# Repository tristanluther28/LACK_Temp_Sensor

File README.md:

# LACK_Temp_Sensor
 Temperature sensor (LM335) with a 4 digit Seven Segment Display (LTC) output for the LACK 3D Printer Enclosure
 
 Read the full article and motivation here: https://tristanluther.com/projects/lack/

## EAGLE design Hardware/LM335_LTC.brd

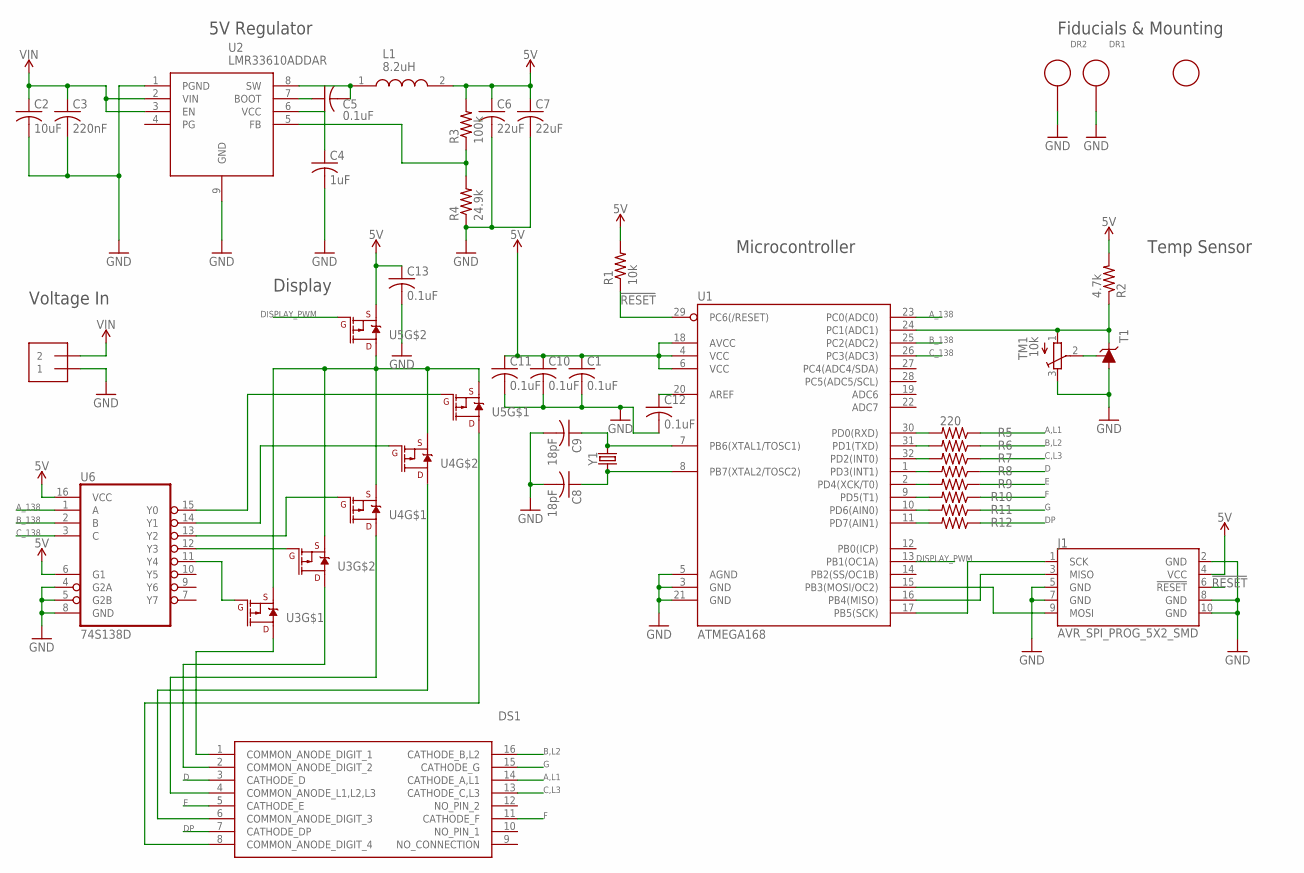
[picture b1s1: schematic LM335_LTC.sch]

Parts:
C1, C5, C10, C11, C12, C13: 0.1uF; C0805
C2: 10uF; C0805
C3: 220nF; C0805
C4: 1uF; C0805
C6, C7: 22uF; C0805
C8, C9: 18pF; C0805
DR1, DR2: 3MM_DRILL_GND
DS1: LTC-4627WC; DIPS1016W50P254L4018H725Q16N
J1: AVR_SPI_PROG_5X2_SMD; SAMTECH_FTSH-105-01
L1: 8.2uH; INDPM5752X150N
R1: 10k; R0805
R2: 4.7k; R0805
R3: 100k; R0805
R4: 24.9k; R0805
R5, R6, R7, R8, R9, R10, R11, R12: 220; R0805
T1: LM335; TO92
TM1: 10k; TC33X
U1: ATMEGA168; TQFP32-08
U2: LMR33610ADDAR; SOIC127P600X170-9N
U3, U4, U5: SI1967DH-T1-E3; SOT363_PHILIPS
U6: 74S138D; SO16
U$2: 25-B200-02; 25−B200-02
U$4: FIDUCIAL; FIDUCIAL_1MM
Y1: 16MHz; CRYSTAL-SMD-5X3.2-4PAD

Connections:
5V: C1.1, C6.1, C7.1, C10.1, C11.1, C13.1, J1.4 (VCC), L1.2, R1.2, R2.2, R3.2, U1.4 (VCC), U1.6 (VCC), U1.18 (AVCC), U5.4 (S), U6.6 (G1), U6.16 (VCC)
!RESET: J1.6 (!RESET), R1.1, U1.29 (PC6(/RESET))
A,L1: DS1.14 (CATHODE_A,L1), R5.1
A_138: U1.23 (PC0(ADC0)), U6.1 (A)
B,L2: DS1.16 (CATHODE_B,L2), R6.1
B_138: U1.25 (PC2(ADC2)), U6.2 (B)
C,L3: DS1.13 (CATHODE_C,L3), R7.1
C_138: U1.26 (PC3(ADC3)), U6.3 (C)
D: DS1.3 (CATHODE_D), R8.1
DISPLAY_PWM: U1.13 (PB1(OC1A)), U5.5 (G)
DP: DS1.7 (CATHODE_DP), R12.1
E: DS1.5 (CATHODE_E), R9.1
F: DS1.11 (CATHODE_F), R10.1
G: DS1.15 (CATHODE_G), R11.1
GND: C1.2, C2.2, C3.2, C4.2, C6.2, C7.2, C8.2, C9.2, C10.2, C11.2, C12.2, C13.2, DR1.DR, DR2.DR, J1.2 (GND), J1.5 (GND), J1.7 (GND), J1.8 (GND), J1.10 (GND), R4.1, T1.2 (A), TM1.3 (E), U1.3 (GND), U1.5 (AGND), U1.21 (GND), U2.1 (PGND), U2.9 (GND), U6.4 (G2A), U6.5 (G2B), U6.8 (GND), U$2.P1 (1)
unnamed: C4.1, U2.6 (VCC)
unnamed: R3.1, R4.2, U2.5 (FB)
unnamed: U3.2 (G), U6.11 (Y4)
unnamed: R2.1, T1.1 (C), TM1.1 (A), U1.24 (PC1(ADC1))
unnamed: C5.2, L1.1, U2.8 (SW)
unnamed: C5.1, U2.7 (BOOT)
unnamed: T1.3 (ADJ), TM1.2 (S)
unnamed: C9.1, U1.7 (PB6(XTAL1/TOSC1)), Y1.3 (2)
unnamed: C8.1, U1.8 (PB7(XTAL2/TOSC2)), Y1.1
unnamed: J1.1 (SCK), U1.17 (PB5(SCK))
unnamed: J1.3 (MISO), U1.16 (PB4(MISO))
unnamed: J1.9 (MOSI), U1.15 (PB3(MOSI/OC2))
unnamed: U3.5 (G), U6.12 (Y3)
unnamed: U4.2 (G), U6.13 (Y2)
unnamed: U4.5 (G), U6.14 (Y1)
unnamed: U5.2 (G), U6.15 (Y0)
unnamed: U3.1 (S), U3.4 (S), U4.1 (S), U4.4 (S), U5.1 (S), U5.3 (D)
unnamed: C12.1, U1.20 (AREF)
unnamed: DS1.1 (COMMON_ANODE_DIGIT_1), U3.6 (D)
unnamed: DS1.2 (COMMON_ANODE_DIGIT_2), U3.3 (D)
unnamed: DS1.4 (COMMON_ANODE_L1,L2,L3), U4.6 (D)
unnamed: DS1.6 (COMMON_ANODE_DIGIT_3), U4.3 (D)
unnamed: DS1.8 (COMMON_ANODE_DIGIT_4), U5.6 (D)
unnamed: R5.2, U1.30 (PD0(RXD))
unnamed: R6.2, U1.31 (PD1(TXD))
unnamed: R7.2, U1.32 (PD2(INT0))
unnamed: R8.2, U1.1 (PD3(INT1))
unnamed: R9.2, U1.2 (PD4(XCK/T0))
unnamed: R10.2, U1.9 (PD5(T1))
unnamed: R11.2, U1.10 (PD6(AIN0))
unnamed: R12.2, U1.11 (PD7(AIN1))
VIN: C2.1, C3.1, U2.2 (VIN), U2.3 (EN), U$2.P2 (2)

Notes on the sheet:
5V Regulator
Microcontroller
Temp Sensor
Display
Voltage In
Fiducials & Mounting

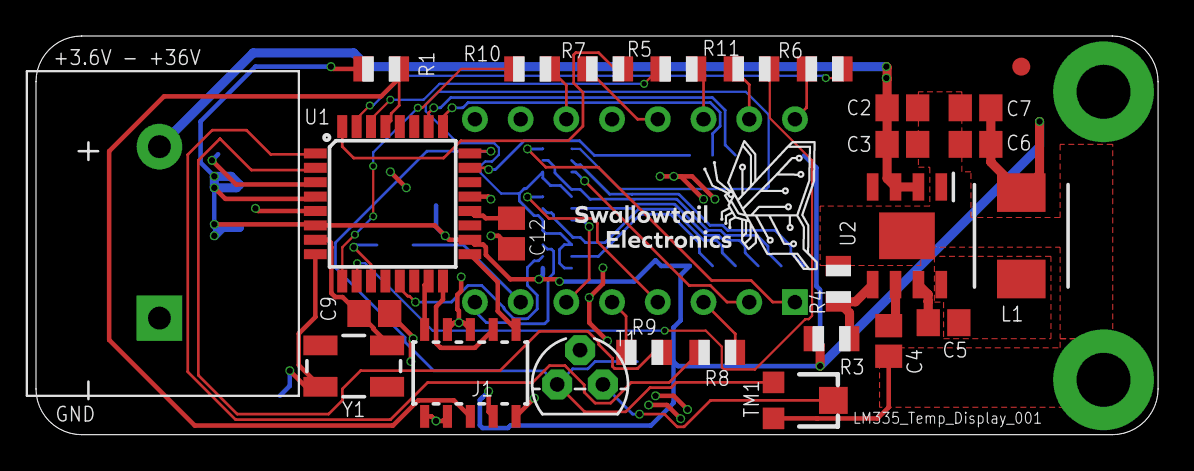
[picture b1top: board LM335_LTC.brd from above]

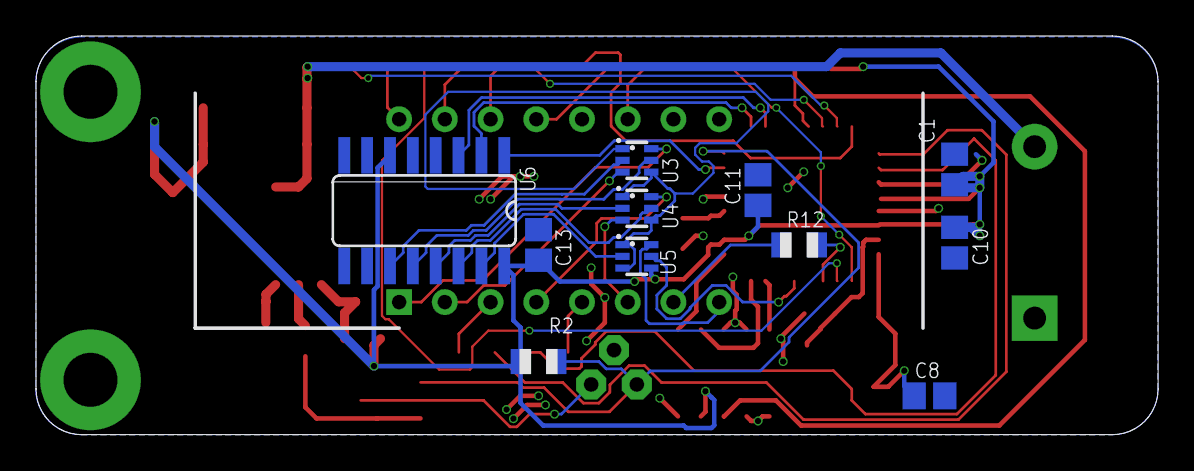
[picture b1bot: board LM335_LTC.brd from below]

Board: 2 copper layers, 62.3 x 22.1 mm, 42 parts (12 on the bottom side), 47 nets.

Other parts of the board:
U$3: SWALLOWTAIL_LOGO_SMALL

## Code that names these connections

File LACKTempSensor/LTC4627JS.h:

//-----------------------------------------------------------------------------
//
//  LTC4627JS.h
//
//  Swallowtail LTC4627JS Firmware
//  AVR LTC4627JS Firmware
//
//  Copyright (c) 2021 Swallowtail Electronics
//
//  Permission is hereby granted, free of charge, to any person obtaining a
//  copy of this software and associated documentation files (the "Software"),
//  to deal in the Software without restriction, including without limitation
//  the rights to use, copy, modify, merge, publish, distribute, sub-license,
//  and/or sell copies of the Software, and to permit persons to whom the
//  Software is furnished to do so, subject to the following conditions:
//
//  The above copyright notice and this permission notice shall be included in
//  all copies or substantial portions of the Software.
//
//  THE SOFTWARE IS PROVIDED "AS IS", WITHOUT WARRANTY OF ANY KIND, EXPRESS OR
//  IMPLIED, INCLUDING BUT NOT LIMITED TO THE WARRANTIES OF MERCHANTABILITY,
//  FITNESS FOR A PARTICULAR PURPOSE AND NONINFRINGEMENT. IN NO EVENT SHALL THE
//  AUTHORS OR COPYRIGHT HOLDERS BE LIABLE FOR ANY CLAIM, DAMAGES OR OTHER
//  LIABILITY, WHETHER IN AN ACTION OF CONTRACT, TORT OR OTHERWISE, ARISING
//  FROM, OUT OF OR IN CONNECTION WITH THE SOFTWARE OR THE USE OR OTHER
//  DEALINGS IN THE SOFTWARE.
//
//  Web:    http://tristanluther.com
//  Email:  tristanluther28@gmail.com
//
//-----------------------------------------------------------------------------

/******************** Include Guard **************************/

#ifndef LTC4627JS_H_
#define LTC4627JS_H_

#ifndef F_CPU
#define F_CPU 1000000UL //Set clock speed to 1MHz
#endif

#include <avr/io.h>
#include <util/delay.h>
#include "PWM.h"

/******************* Macros **********************************/

#define BIT_SET(byte, bit) (byte & (1<<bit))

#define ON                        1
#define OFF                       0

#define LTC4627JS_MODE_INTENSITY    0x0A
#define LTC4627JS_MODE_NOOP         0x00
#define LTC4627JS_CHAR_BLANK        0xFF
#define LTC4627JS_CHAR_NEGATIVE     0xA

//74HC138 Connections
#define DDR_138 DDRC
#define PORT_138 PORTC
#define A_138 PC0
#define B_138 PC2
#define C_138 PC3

#define LTC4627JS_DIGIT0            0x08
#define LTC4627JS_DIGIT1            0x05
#define LTC4627JS_DIGIT2            0x01
#define LTC4627JS_DIGIT3            0x00
#define LTC4627JS_L					0x04

//Seven Segment Connections
#define DDR_SEG DDRD
#define PORT_SEG PORTD
#define A_L1 PD0
#define B_L2 PD1
#define C_L3 PD2
#define D PD3
#define E PD4
#define F PD5
#define G PD6
#define DP PD7
#define LTC4627JS_ONE 0x79
#define LTC4627JS_TWO 0x24
#define LTC4627JS_THREE 0x30
#define LTC4627JS_FOUR 0x19
#define LTC4627JS_FIVE 0x12
#define LTC4627JS_SIX 0x02
#define LTC4627JS_SEVEN 0x78
#define LTC4627JS_EIGHT 0x00
#define LTC4627JS_NINE 0x10
#define LTC4627JS_ZERO 0x40
#define LTC4627JS_C 0x46
#define LTC4627JS_F 0x8E
#define LTC4627JS_K 0x05
#define LTC4627JS_L3 0x03

/******************* Function Declarations *******************/

void LTC4627JS_Init();
void LTC4627JS_Write(uint8_t, uint8_t);
void LTC4627JS_Display4Digit(uint16_t);
void LTC4627JS_DisplayTemp(uint16_t, uint8_t);

#endif

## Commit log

2021-08-16 Added ATmega328P Internal Temperature Sensor for ADC.c
2021-08-16 Added EAGLE board and schematic and Fusion 360 Enclosure

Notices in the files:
parts and their libraries:
SparkFun-PowerSymbols: Licensing: Creative Commons ShareAlike 4.0 International - https://creativecommons.org/licenses/by-sa/4.0
